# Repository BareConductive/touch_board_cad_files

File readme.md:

# Bare Conductive Touch Board CAD files
These are the CAD files of the [Touch Board](http://www.bareconductive.com/shop/touch-board/).

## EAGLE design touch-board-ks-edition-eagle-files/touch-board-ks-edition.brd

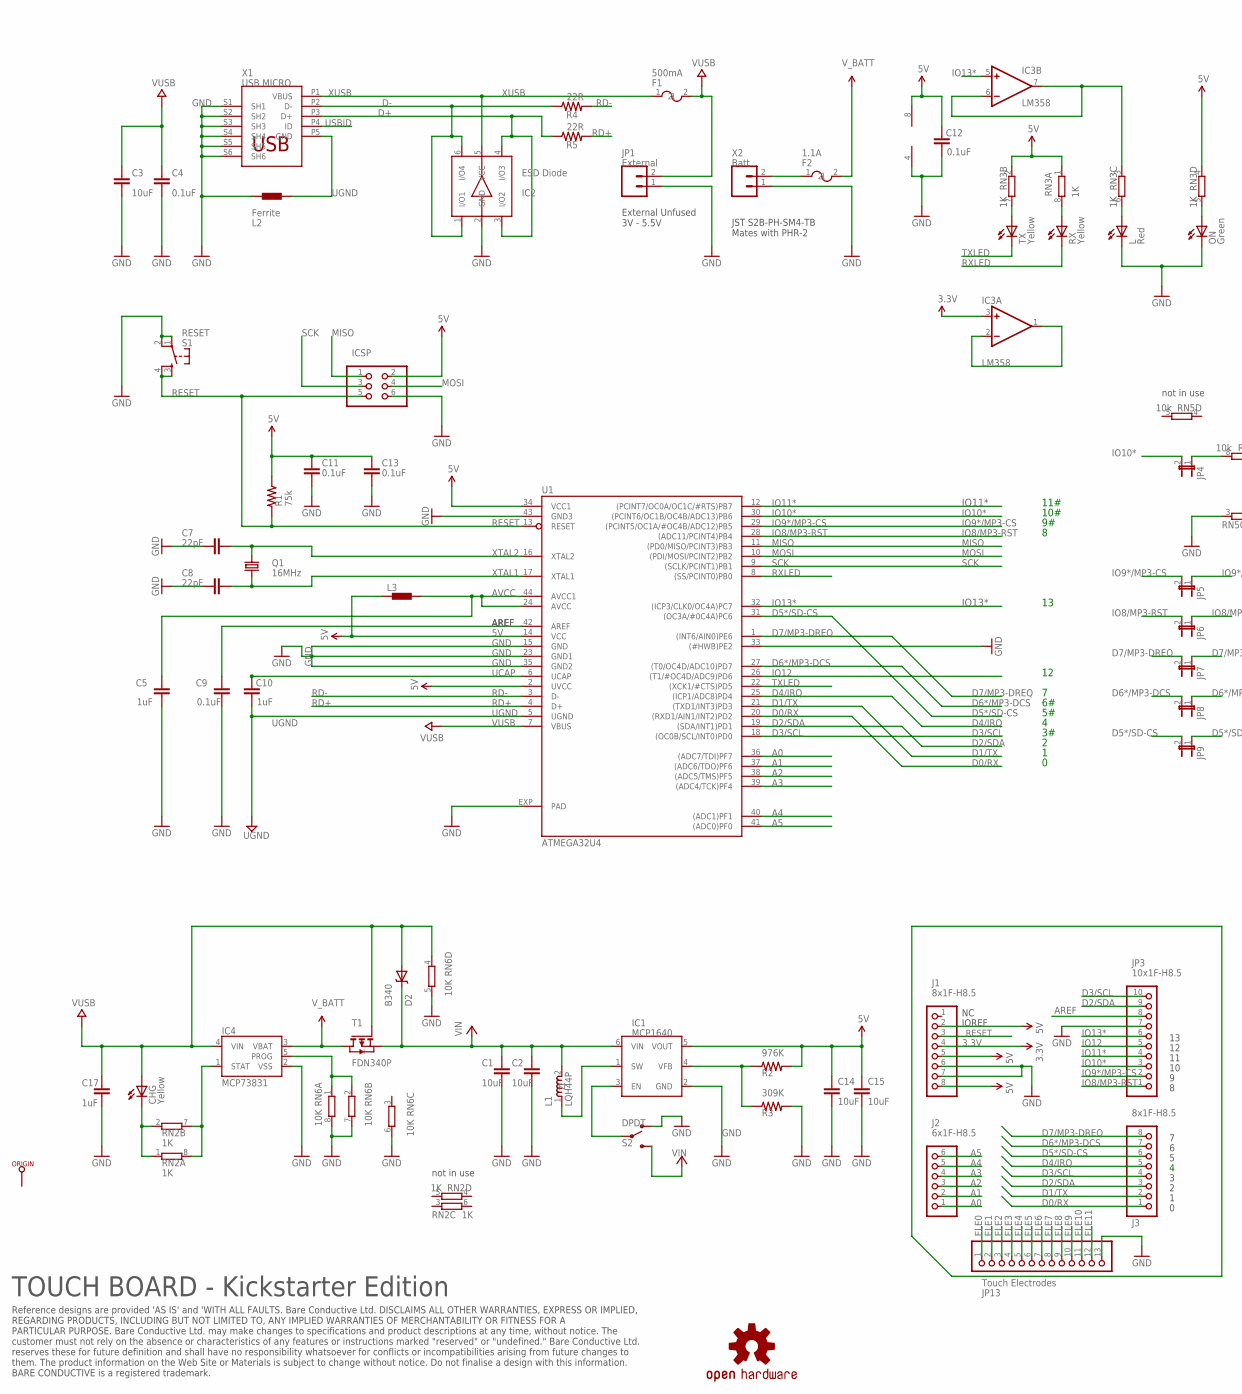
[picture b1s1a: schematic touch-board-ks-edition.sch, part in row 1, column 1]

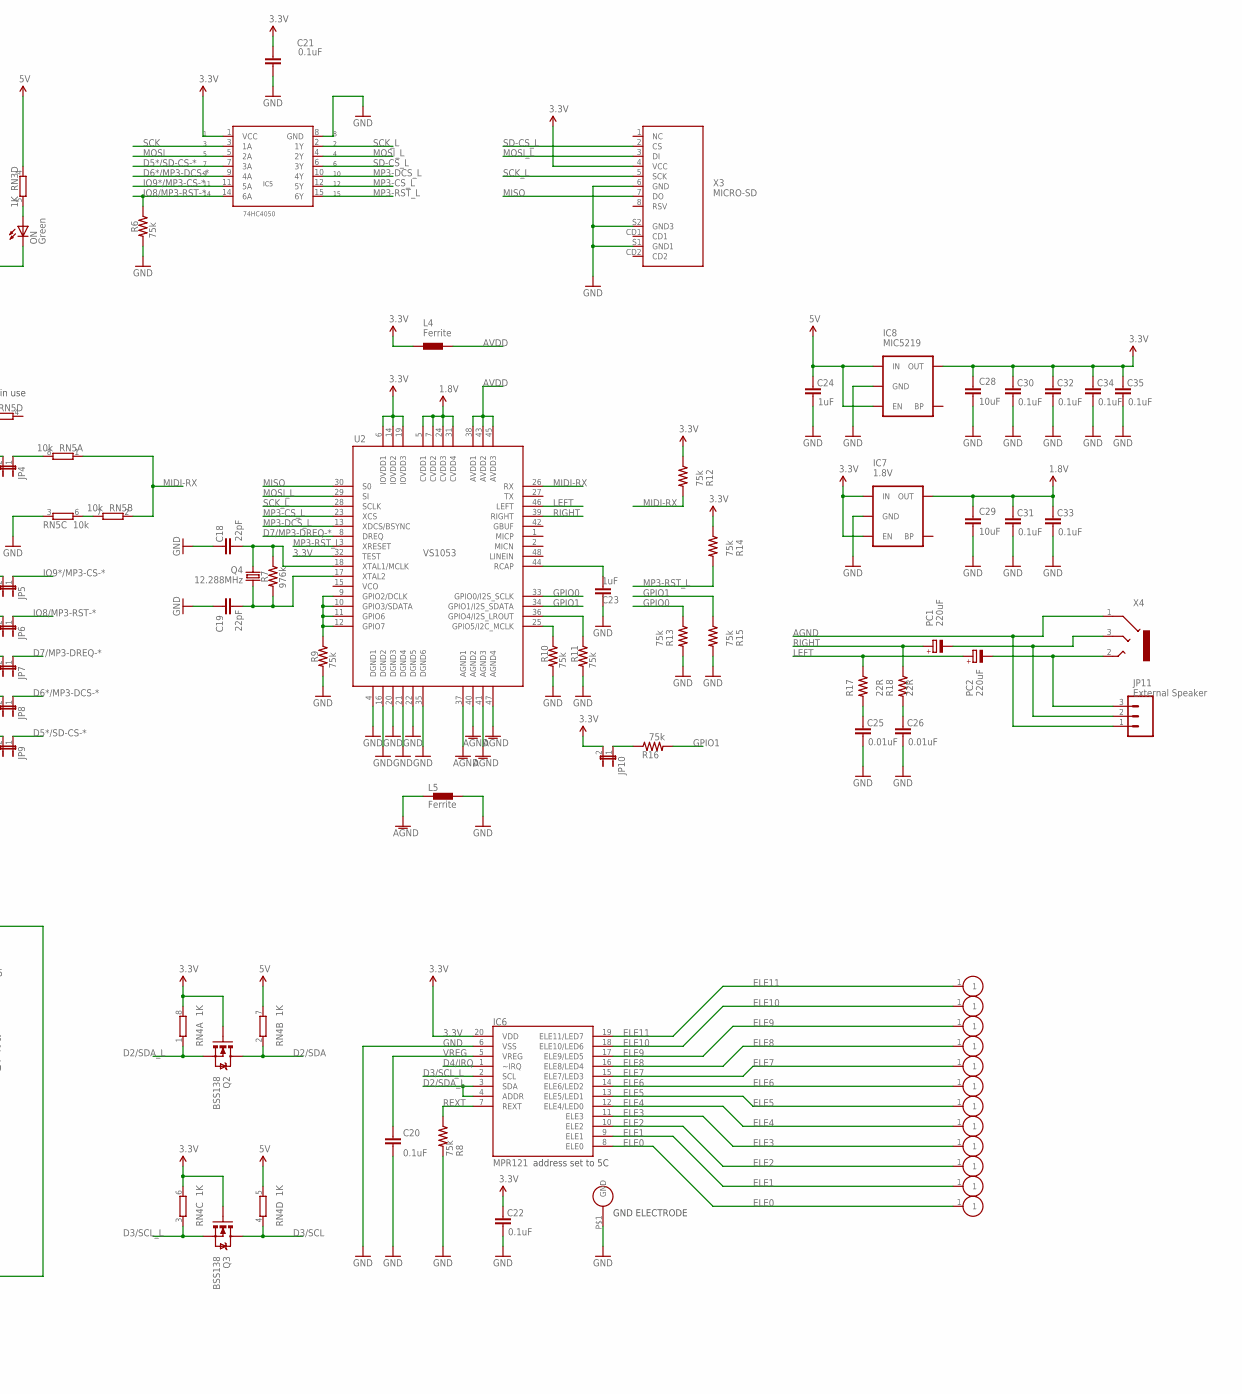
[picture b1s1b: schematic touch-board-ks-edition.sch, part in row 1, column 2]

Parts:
C1, C2, C3, C14, C15, C28, C29: 10uF; 1206
C4, C9, C11, C12, C13, C20, C21, C22, C30, C31, C32, C33, C34, C35: 0.1uF; 0402-CAP
C5, C10, C17, C23, C24: 1uF; 0402-CAP
C7, C8, C18, C19: 22pF; 0402-CAP
C25, C26: 0.01uF; 0402-CAP
CHG: Yellow; CHIPLED_0805
D2: B340; SMA-DIODE
F1: 500mA; 0805
F2: 1.1A; 0805
IC1: MCP1640; 6-LEAD-SOT23
IC2: ESD Diode; SOT457
IC3: LM358; MSOP08
IC4: MCP73831; SOT23-5
IC5: 74HC4050; TSSOP-16
IC6: MPR121; QFN-20-0.4MM
IC7: 1.8V; SC70
IC8: MIC5219; SOT23-5
ICSP: ICSP; 2X03
J1, J3: 8x1F-H8.5; 1X08
J2: 6x1F-H8.5; 1X06
JP1: External; 1X02
JP3: 10x1F-H8.5; 1X10
JP4, JP10: JUMPER-2SMD-NO; SJ_2S-NO
JP5, JP6, JP7, JP8, JP9: JUMPER-2SMD-NC; SJ_2S
JP11: External Speaker; 1X03
JP13: Touch Electrodes; 1X13
L: Red; CHIPLED_0805
L1: LQH44P; LQH44PN100MP0L
L2, L4, L5: Ferrite; 0402
L3: BLM15HB121SN1; 0402
ON: Green; CHIPLED_0805
ORIGIN: TP_SP; TP-SP
PC1, PC2: 220uF; PANASONIC_D
Q1: 16MHz; CRYSTAL-SMD-5X3
Q2, Q3: BSS138; SOT23-3
Q4: 12.288MHz; CRYSTAL-SMD-5X3
R1, R6, R8, R9, R10, R11, R12, R13, R14, R15, R16: 75k; 0402-RES
R2: 976K; 0402-RES
R3: 309K; 0402-RES
R4, R5, R17, R18: 22R; 0402-RES
R7: 976k; 0402-RES
RN2, RN3, RN4: 1K; CAY16
RN5: 10k; CAY16
RN6: 10K; CAY16
RX: Yellow; CHIPLED_0805
S1: RESET; TACTILE_SWITCH_SMD@1
S2: DPDT; JS202011SCQN
T1: FDN340P; SOT-23
TX: Yellow; CHIPLED_0805
U1: ATMEGA32U4; QFN44ML7X7
U2: VS1053; LQFP-48
U$1: EDGE-ELEC-LEFT
U$3: EDGE-ELEC-RIGHT
U$6: EDGE-GND
U$8: OSHW-LOGO
U$17, U$18, U$22, U$24, U$26, U$27, U$28, U$29, U$30, U$31: EDGE-ELEC
X1: USB MICRO; CON2_USB_MICRO_B_AT
X2: Batt; JST-2-SMD
X3: MICRO-SD; MSDC-PP-02
X4: SJ-3523; 3POLE-JACK

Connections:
1.8V: C29.1, C31.2, C33.2, IC7.5 (OUT), U2.5 (CVDD1), U2.7 (CVDD2), U2.24 (CVDD3), U2.31 (CVDD4)
3.3V: C21.2, C22.2, C28.1, C30.2, C32.2, C34.2, C35.2, IC3.3 (+IN), IC5.1 (VCC), IC6.20 (VDD), IC7.1 (IN), IC7.3 (EN), IC8.5 (OUT), J1.4, JP10.2, L4.1, Q2.1 (G), Q3.1 (G), R12.1, R14.1, RN4.6 (2), RN4.8 (2), U2.6 (IOVDD1), U2.14 (IOVDD2), U2.19 (IOVDD3), U2.32 (TEST), X3.4 (VCC)
5V: C11.2, C12.2, C13.2, C14.1, C15.1, C24.2, IC1.5 (VOUT), IC3.8 (V+), IC8.1 (IN), IC8.3 (EN), ICSP.2, J1.2, J1.5, J1.8, L3.1, R1.1, R2.2, RN3.1, RN3.2 (1), RN3.4 (1), RN4.5 (2), RN4.7 (2), U1.2 (UVCC), U1.14 (VCC), U1.34 (VCC1)
A0: J2.1, U1.36 ((ADC7/TDI)PF7)
A1: J2.2, U1.37 ((ADC6/TDO)PF6)
A2: J2.3, U1.38 ((ADC5/TMS)PF5)
A3: J2.4, U1.39 ((ADC4/TCK)PF4)
A4: J2.5, U1.40 ((ADC1)PF1)
A5: J2.6, U1.41 ((ADC0)PF0)
AGND: JP11.1, L5.1, U2.37 (AGND1), U2.40 (AGND2), U2.41 (AGND3), U2.47 (AGND4), X4.1
AREF: C9.2, JP3.8, U1.42 (AREF)
AVCC: C5.2, L3.2, U1.24 (AVCC), U1.44 (AVCC1)
AVDD: L4.2, U2.38 (AVDD1), U2.43 (AVDD2), U2.45 (AVDD3)
D0/RX: J3.1, U1.20 ((RXD1/AIN1/INT2)PD2)
D1/TX: J3.2, U1.21 ((TXD1/INT3)PD3)
D2/SDA: J3.3, JP3.9, Q2.3 (D), RN4.2 (1), U1.19 ((SDA/INT1)PD1)
D2/SDA_L: IC6.3 (SDA), IC6.4 (ADDR), Q2.2 (S), RN4.1
D3/SCL: J3.4, JP3.10, Q3.3 (D), RN4.4 (1), U1.18 ((OC0B/SCL/INT0)PD0)
D3/SCL_L: IC6.2 (SCL), Q3.2 (S), RN4.3 (1)
D4/IRQ: IC6.1 (~IRQ), J3.5, U1.25 ((ICP1/ADC8)PD4)
D5*/SD-CS: J3.6, JP9.2, U1.31 ((OC3A/#0C4A)PC6)
D5*/SD-CS-*: IC5.7 (3A), JP9.1
D6*/MP3-DCS: J3.7, JP8.2, U1.27 ((T0/OC4D/ADC10)PD7)
D6*/MP3-DCS-*: IC5.9 (4A), JP8.1
D7/MP3-DREQ: J3.8, JP7.2, U1.1 ((INT6/AIN0)PE6)
D7/MP3-DREQ-*: JP7.1, U2.8 (DREQ)
D+: IC2.3 (I/O2), IC2.4 (I/O3), R5.1, X1.P3 (D+)
D-: IC2.1 (I/O1), IC2.6 (I/O4), R4.1, X1.P2 (D-)
ELE0: IC6.8 (ELE0), JP13.1, U$1.1
ELE1: IC6.9 (ELE1), JP13.2, U$31.1
ELE2: IC6.10 (ELE2), JP13.3, U$30.1
ELE3: IC6.11 (ELE3), JP13.4, U$29.1
ELE4: IC6.12 (ELE4/LED0), JP13.5, U$28.1
ELE5: IC6.13 (ELE5/LED1), JP13.6, U$27.1
ELE6: IC6.14 (ELE6/LED2), JP13.7, U$26.1
ELE7: IC6.15 (ELE7/LED3), JP13.8, U$24.1
ELE8: IC6.16 (ELE8/LED4), JP13.9, U$22.1
ELE9: IC6.17 (ELE9/LED5), JP13.10, U$18.1
ELE10: IC6.18 (ELE10/LED6), JP13.11, U$17.1
ELE11: IC6.19 (ELE11/LED7), JP13.12, U$3.1
G1: R9.1, U2.9 (GPIO2/DCLK), U2.10 (GPIO3/SDATA), U2.11 (GPIO6), U2.12 (GPIO7)
G2: R10.1, U2.25 (GPIO5/I2C_MCLK)
GND: C1.2, C2.2, C3.2, C4.1, C5.1, C7.2, C8.2, C9.1, C11.1, C12.1, C13.1, C14.2, C15.2, C17.1, C18.2, C19.2, C20.1, C21.1, C22.1, C23.2, C24.1, C25.1, C26.1, C28.2, C29.2, C30.1, C31.1, C32.1, C33.1, C34.1, C35.1, IC1.2 (GND), IC2.2 (GND), IC3.4 (V-), IC4.2 (VSS), IC5.8 (GND), IC6.6 (VSS), IC7.2 (GND), IC8.2 (GND), ICSP.6, J1.6, J1.7, JP1.1, JP3.7, JP13.13, L.C, L2.1, L5.2, ON.C, R3.2, R6.2, R8.2, R9.2, R10.2, R11.2, R13.2, R15.2, RN5.3 (1), RN6.5 (2), RN6.6 (2), RN6.7 (2), RN6.8 (2), S1.1, S1.2, S2.4, U1.15 (GND), U1.23 (GND1), U1.33 ((#HWB)PE2), U1.35 (GND2), U1.43 (GND3), U1.EXP (PAD), U2.4 (DGND1), U2.16 (DGND2), U2.20 (DGND3), U2.21 (DGND4), U2.22 (DGND5), U2.35 (DGND6), U$6.P$1, X1.S1 (SH1), X1.S2 (SH2), X1.S3 (SH3), X1.S4 (SH4), X1.S5 (SH5), X1.S6 (SH6), X2.1, X3.6 (GND), X3.S1 (GND1), X3.S2 (GND3)
GPIO0: R13.1, U2.33 (GPIO0/I2S_SCLK)
GPIO1: R15.1, R16.2, U2.34 (GPIO1/I2S_SDATA)
IO8/MP3-RST: JP3.1, JP6.2, U1.28 ((ADC11/PCINT4)PB4)
IO8/MP3-RST-*: IC5.14 (6A), JP6.1, R6.1
IO9*/MP3-CS: JP3.2, JP5.2, U1.29 ((PCINT5/OC1A/#OC4B/ADC12)PB5)
IO9*/MP3-CS-*: IC5.11 (5A), JP5.1
IO10*: JP3.3, JP4.2, U1.30 ((PCINT6/OC1B/OC4B/ADC13)PB6)
IO11*: JP3.4, U1.12 ((PCINT7/OC0A/OC1C/#RTS)PB7)
IO12: JP3.5, U1.26 ((T1/#OC4D/ADC9)PD6)
IO13*: IC3.5 (+IN), JP3.6, U1.32 ((ICP3/CLK0/OC4A)PC7)
LEFT: PC2.+, R17.1, U2.46 (LEFT)
MIDI-RX: R12.2, RN5.1, RN5.2 (1), U2.26 (RX)
MISO: ICSP.1, U1.11 ((PD0/MISO/PCINT3)PB3), U2.30 (S0), X3.7 (DO)
MOSI: IC5.5 (2A), ICSP.4, U1.10 ((PDI/MOSI/PCINT2)PB2)
MOSI_L: IC5.4 (2Y), U2.29 (SI), X3.3 (DI)
MP3-CS_L: IC5.12 (5Y), U2.23 (XCS)
MP3-DCS_L: IC5.10 (4Y), U2.13 (XDCS/BSYNC)
MP3-RST_L: IC5.15 (6Y), R14.2, U2.3 (XRESET)
unnamed: IC3.6 (-IN), IC3.7 (OUT), RN3.3 (1)
unnamed: L.A, RN3.6 (2)
unnamed: RN3.7 (2), TX.A
unnamed: IC4.1 (STAT), RN2.7 (2), RN2.8 (2)
unnamed: C23.1, U2.44 (RCAP)
unnamed: RN3.8 (2), RX.A
unnamed: ON.A, RN3.5 (2)
unnamed: C18.1, Q4.3 (2), R7.1, U2.18 (XTAL1/MCLK)
unnamed: C19.1, Q4.1, R7.2, U2.17 (XTAL2)
unnamed: IC1.1 (SW), L1.1
unnamed: IC1.4 (VFB), R2.1, R3.1
unnamed: F2.1, X2.2
unnamed: JP4.1, RN5.8 (2)
unnamed: IC3.1 (OUT), IC3.2 (-IN)
unnamed: IC4.5 (PROG), RN6.1, RN6.2 (1)
unnamed: C25.2, R17.2
unnamed: C26.2, R18.2
unnamed: IC1.3 (EN), S2.5
unnamed: JP11.3, PC2.-, X4.2
unnamed: JP10.1, R16.1
unnamed: JP11.2, PC1.-, X4.3
unnamed: RN5.6 (2), RN5.7 (2)
unnamed: CHG.C, RN2.1, RN2.2 (1)
unnamed: R11.1, U2.36 (GPIO4/I2S_LROUT)
RD+: R5.2, U1.4 (D+)
RD-: R4.2, U1.3 (D-)
RESET: ICSP.5, J1.3, R1.2, S1.3, S1.4, U1.13 (RESET)
REXT: IC6.7 (REXT), R8.1
RIGHT: PC1.+, R18.1, U2.39 (RIGHT)
RXLED: RX.C, U1.8 ((SS/PCINT0)PB0)
SCK: IC5.3 (1A), ICSP.3, U1.9 ((SCLK/PCINT1)PB1)
SCK_L: IC5.2 (1Y), U2.28 (SCLK), X3.5 (SCK)
SD-CS_L: IC5.6 (3Y), X3.2 (CS)
TXLED: TX.C, U1.22 ((XCK1/#CTS)PD5)
UCAP: C10.2, U1.6 (UCAP)
UGND: C10.1, L2.2, U1.5 (UGND), X1.P5 (GND)
USBID: X1.P4 (ID)
VCC: C1.1, C2.1, D2.C, IC1.6 (VIN), L1.2, S2.6, T1.2 (S)
VREG: C20.2, IC6.5 (VREG)
VUSB: C3.1, C4.2, C17.2, CHG.A, D2.A, F1.2, IC4.4 (VIN), JP1.2, RN6.4 (1), T1.3 (G), U1.7 (VBUS)
V_BATT: F2.2, IC4.3 (VBAT), T1.1 (D)
XTAL1: C8.1, Q1.1, U1.17 (XTAL1)
XTAL2: C7.1, Q1.3 (2), U1.16 (XTAL2)
XUSB: F1.1, IC2.5 (VCC), X1.P1 (VBUS)

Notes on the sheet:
USB
IOREF
10#
11#
Reference designs are provided 'AS IS' and 'WITH ALL FAULTS. Bare Conductive Ltd. DISCLAIMS ALL OTHER WARRANTIES, EXPRESS OR IMPLIED, REGARDING PRODUCTS, INCLUDING BUT NOT LIMITED TO, ANY IMPLIED WARRANTIES OF MERCHANTABILITY OR FITNESS FOR A PARTICULAR PURPOSE. Bare Conductive Ltd. may make change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
not in use
External Unfused 3V - 5.5V
address set to 5C
TOUCH BOARD - Kickstarter Edition
GND ELECTRODE
JST S2B-PH-SM4-TB Mates with PHR-2

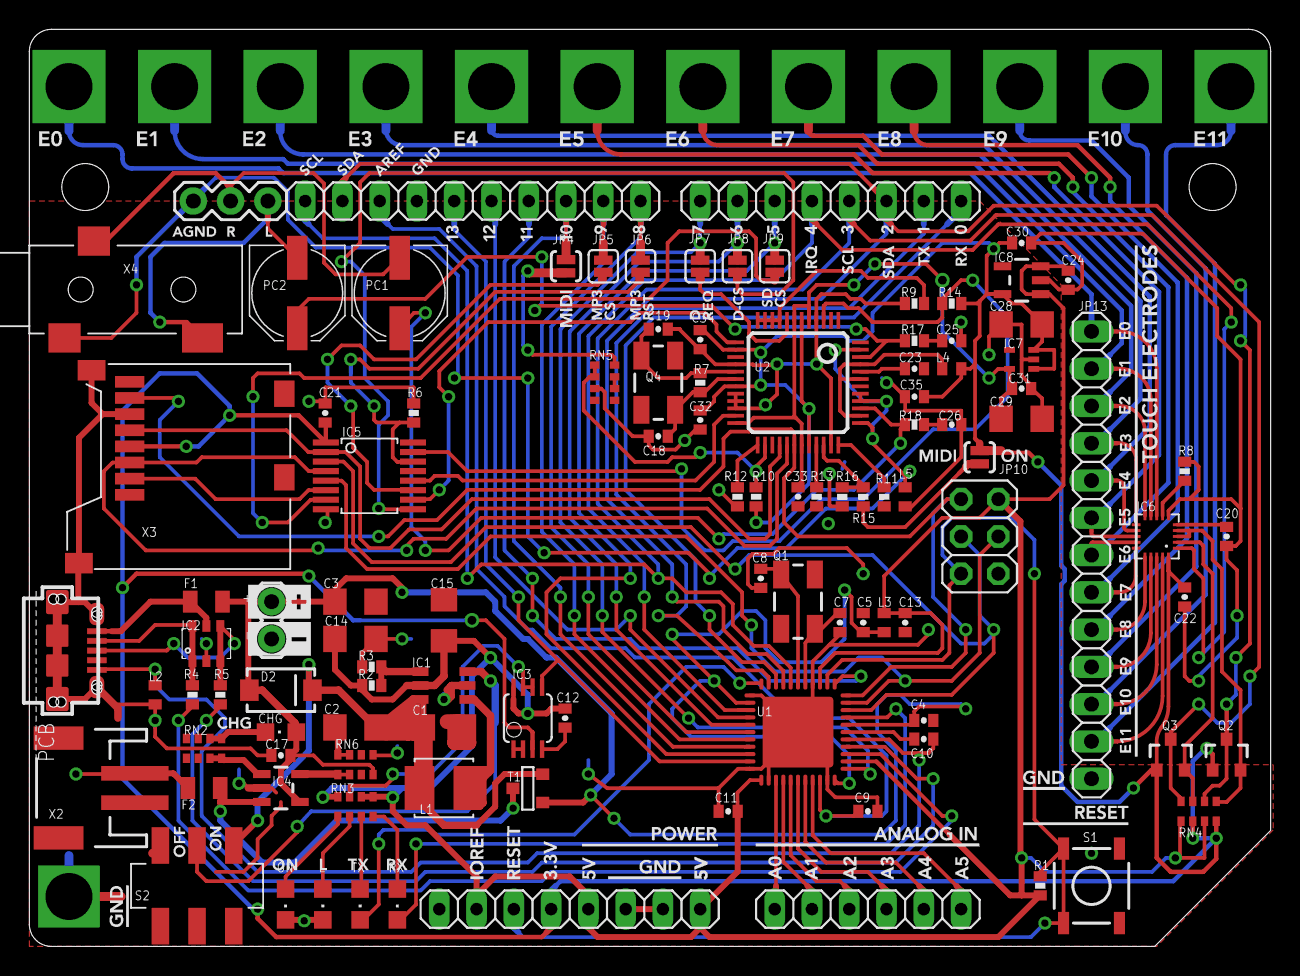
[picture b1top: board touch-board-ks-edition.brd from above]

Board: 2 copper layers, 84.6 x 62.5 mm, 121 parts (0 on the bottom side), 104 nets.

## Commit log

2014-10-06 Inital Commit with Schematic pdf
2014-10-06 Readme and Thank You for backers
2014-10-09 Initial commit for eagel files
2014-10-09 Edit readme
2015-02-24 Updated logo in readme.md
2016-11-03 Updated license
2020-03-27 Renaming files and folders
2020-03-27 Updated README file

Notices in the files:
parts and their libraries:
SparkFun-Passives: Licensing: CC v3.0 Share-Alike You are welcome to use this library for commercial purposes.
